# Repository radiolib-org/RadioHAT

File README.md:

# RadioHAT
Raspberry Pi PCIe HAT for radio modules

This HAT is an all-in-one radio modules development platform with the following features. 

* **Built-in logic analyzer** - All pins routed to the transceivers (SPI and various GPIO signals) are also routed to additional Raspberry Pi GPIO pins, to allow the RPi to monitor and record the state of communication pins. See the [pinalyzer repository](https://github.com/radiolib-org/pinalyzer) for details.
* **Adjustable linear voltage regulator** - To supply power-intensive transceivers, there is a dedicated LDO regulator with adjustable output. The output voltage is adjustable between 2.9 and 3.6 V.
* **Power consumption measurement** - There is a built-in INA219 current monitor which allows to measure the power consumption of the transceiver. See the [dc-powermon repository](https://github.com/radiolib-org/dc-powermon) for details.

While these features are useful, they are entirely optional. Without them, the HAT is a simple adapter board for mini-PCIe cards (half-size or full-size) and can be left with most of the components unpopulated, except for the RPi pin header, PCIe connector and the card latch.

## RadioHAT

## Card for modules from Dorji

## Card for modules from GNice-RF

## Card for modules from Ebyte

## Card for Wio-E5

## Mini PCIe connector pinout
Different vendors (RAK Wireless, Waveshare, SeeedStudio and others) offer radio modules in the mini-PCIe card form factor. However, there seems to be no consensus on any specific pinout. Naturally, RadioLib defines its own version to add to the confusion. However, we try to adhere to the standard Mini PCIe 2.0 pinout in the following ways:

* Mini PCIe 2.0 SMB pins are used for I2C
* Mini PCIe 2.0 USB pins are used for USB
* IRQs, resets and various GPIOs are connected to Mini PCIe 2.0 digital signals
* 3.3V voltage pins are used for most modules, though sometimes 5V is optionally used 

The complete pinout of the connector (and therefore the PCIe cards) is shown below.

| Pin | Signal   | Signal   | Pin |
| --- | -------- | -------- | --- |
|   1 | GPIO0    | 3V3      | 2   |
|   3 | IRQ0     | GND      | 4   |
|   5 | IRQ1     | 5V       | 6   |
|   7 | GPIO1    | NC       | 8   |
|   9 | GND      | NC       | 10  |
|  11 | RST0     | NC       | 12  |
|  13 | RST1     | NC       | 14  |
|  15 | GND      | NC       | 16  |
|  17 | NC       | GND      | 18  |
|  19 | NC       | NSS1     | 20  |
|  21 | GND      | NC       | 22  |
|  23 | NC       | 3V3      | 24  |
|  25 | NC       | GND      | 26  |
|  27 | GND      | 5V       | 28  |
|  29 | GND      | I2C_SCL  | 30  |
|  31 | PPS      | I2C_SDA  | 32  |
|  33 | NC       | GND      | 34  |
|  35 | GND      | USB_D-   | 36  |
|  37 | GND      | USB_D+   | 38  |
|  39 | 3V3      | GND      | 40  |
|  41 | 3V3      | LED0     | 42  |
|  43 | GND      | LED1     | 44  |
|  45 | SPI_SCK  | LED2     | 46  |
|  47 | SPI_MISO | 5V       | 48  |
|  49 | SPI_MOSI | GND      | 50  |
|  51 | NSS0     | 3V3      | 52  |

## Raspberry Pi pinout

The shield routes the Mini PCIe connector signals to the following Raspberry Pi GPIO header pins. The pins with prefix `SNS_` are connected to the digital signals through a series resistor and GPIO, allowing to use the RPi as a makeshift logic analyzer.

| Pin | Signal    | Signal    | Pin |
| --- | --------- | --------- | --- |
|   1 | 3V3       | 5V        | 2   |
|   3 | I2C_SCL   | 5V        | 4   |
|   5 | I2C_SDA   | GND       | 6   |
|   7 | SNS_NSS0  | SNS_SDA   | 8   |
|   9 | GND       | SNS_SCL   | 10  |
|  11 | SNS_SCK   | RST0      | 12  |
|  13 | SNS_MISO  | GND       | 14  |
|  15 | SNS_MOSI  | GPIO1     | 16  |
|  17 | 3V3       | IRQ1      | 18  |
|  19 | SPI_MOSI  | GND       | 20  |
|  21 | SPI_MISO  | RST1      | 22  |
|  23 | SPI_SCK   | NSS0      | 24  |
|  25 | GND       | NSS1      | 26  |
|  27 | NC        | NC        | 28  |
|  29 | SNS_IRQ0  | GND       | 30  |
|  31 | SNS_RST0  | SNS_GPIO0 | 32  |
|  33 | SNS_NSS1  | GND       | 34  |
|  35 | SNS_IRQ1  | IRQ0      | 36  |
|  37 | SNS_GPIO1 | GPIO0     | 38  |
|  39 | GND       | SNS_RST1  | 40  |

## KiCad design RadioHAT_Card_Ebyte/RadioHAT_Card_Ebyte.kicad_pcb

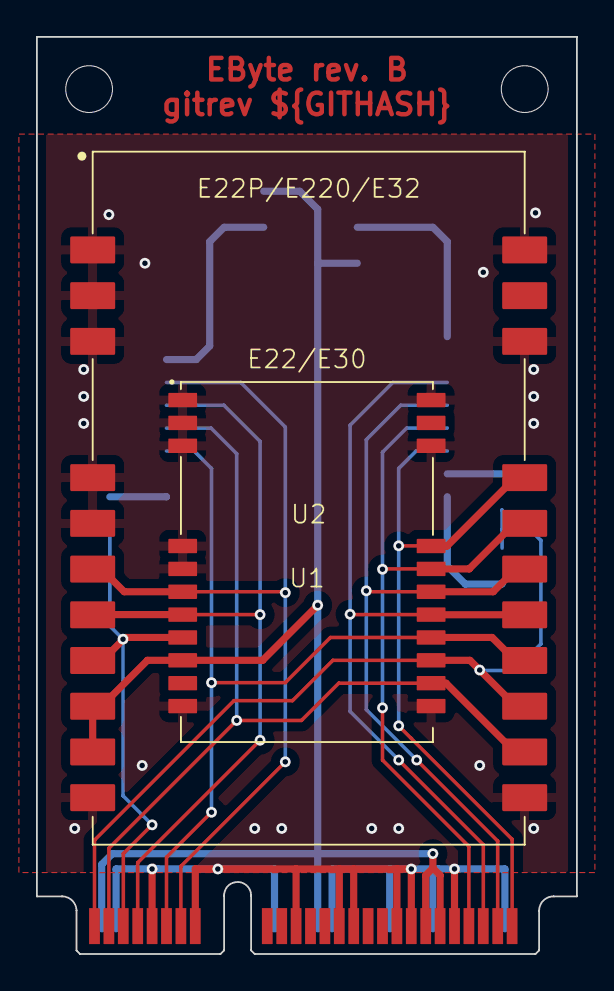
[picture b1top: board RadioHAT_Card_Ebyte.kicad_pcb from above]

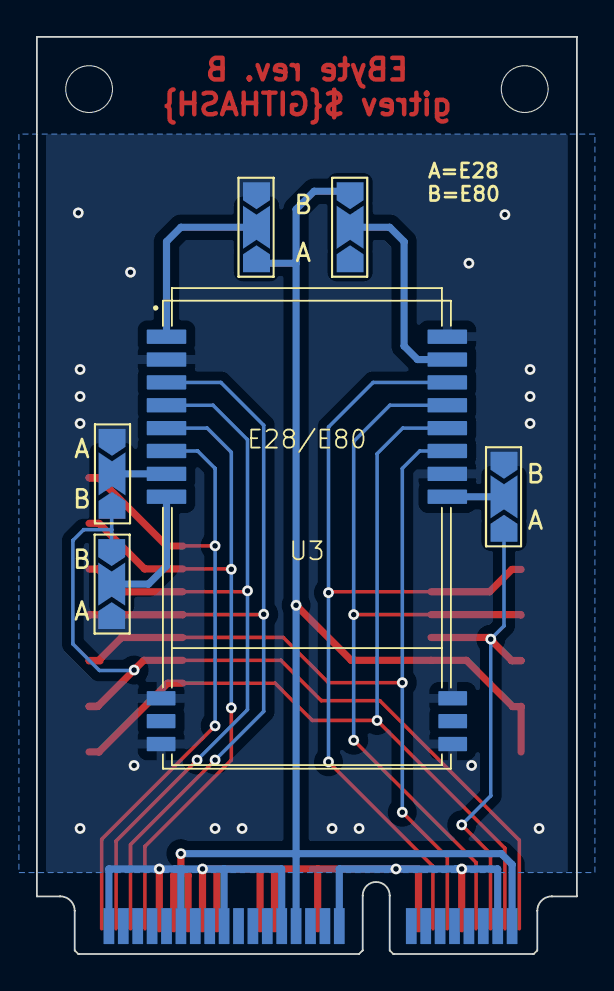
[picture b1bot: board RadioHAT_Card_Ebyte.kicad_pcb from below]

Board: 2 copper layers, 30.0 x 50.9 mm, 9 parts (6 on the bottom side), 17 nets.

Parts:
J1: Mini_PCIe_Full
JP1, JP2, JP3, JP4, JP5: SolderJumper_3_Open; SolderJumper-3_P2.0mm_Open_TrianglePad1.0x1.5mm_NumberLabels
U1: E22_Small
U2: E22_Large
U3: E28_E80

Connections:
+3V3: J1.2 (3V3), J1.24 (3V3), J1.39 (3V3), J1.41 (3V3), JP1.3 (B), JP2.1 (A), U1.9 (VCC), U2.9 (VCC), U2.10 (VCC)
GND: J1.4 (GND), J1.9 (GND), J1.15 (GND), J1.18 (GND), J1.21 (GND), J1.26 (GND), J1.27 (GND), J1.29 (GND), J1.34 (GND), J1.35 (GND), J1.37 (GND), J1.40 (GND), J1.43 (GND), J1.50 (GND), JP2.3 (B), JP3.3 (B), JP4.3 (B), JP5.1 (A), U1.1 (GND), U1.2 (GND), U1.3 (GND), U1.4 (GND), U1.5 (GND), U1.11 (GND), U1.12 (GND), U1.20 (GND_ANT), U1.22 (GND_ANT), U2.1 (GND), U2.2 (GND), U2.3 (GND), U2.4 (GND), U2.5 (GND), U2.11 (GND), U2.12 (GND), U2.20 (GND_ANT), U2.22 (GND_ANT), U3.2 (GND), U3.11 (GND_ANT), U3.13 (GND_ANT), U3.14 (GND_ANT), U3.16 (GND_ANT), U3.20 (GND), U3.26 (GND)
GPIO0: J1.1 (GPIO0), JP3.1 (A), JP5.3 (B), U1.14 (BUSY), U2.14 (BUSY)
GPIO1: J1.7 (GPIO1), U1.7 (TXEN), U2.7 (TXEN), U3.23 (DIO8/DIO1)
IRQ0: J1.3 (IRQ0), U1.13 (DIO1), U2.13 (DIO1), U3.22 (DIO9/BUSY)
IRQ1: J1.5 (IRQ1), JP4.1 (A), U1.8 (DIO2), U2.8 (DIO2)
MISO: J1.47 (SPI_MISO), U1.16 (MISO), U2.16 (MISO), U3.3 (MISO)
MOSI: J1.49 (SPI_MOSI), U1.17 (MOSI), U2.17 (MOSI), U3.4 (MOSI)
NSS: J1.51 (NSS0), U1.19 (NSS), U2.19 (NSS), U3.6 (NSS)
unnamed: JP1.2 (C), U3.25 (VCC/DIO3)
unnamed: JP2.2 (C), U3.1 (GND/VCC)
unnamed: JP3.2 (C), U3.8 (GND/RX_EN)
unnamed: JP4.2 (C), U3.19 (GND/TX_EN)
unnamed: JP5.2 (C), U3.7 (BUSY/GND)
RST0: J1.11 (RST0), U1.15 (NRST), U2.15 (NRST), U3.21 (NRST)
RST1: J1.13 (RST1), U1.6 (RXEN), U2.6 (RXEN), U3.24 (DIO7/DIO2)
SCK: J1.45 (SPI_SCK), U1.18 (SCK), U2.18 (SCK), U3.5 (SCK)

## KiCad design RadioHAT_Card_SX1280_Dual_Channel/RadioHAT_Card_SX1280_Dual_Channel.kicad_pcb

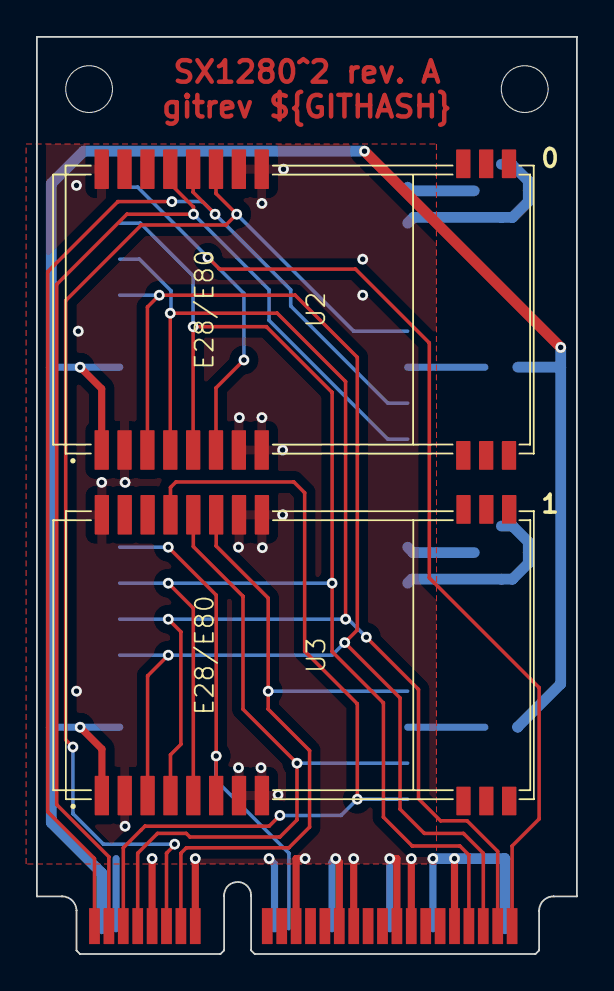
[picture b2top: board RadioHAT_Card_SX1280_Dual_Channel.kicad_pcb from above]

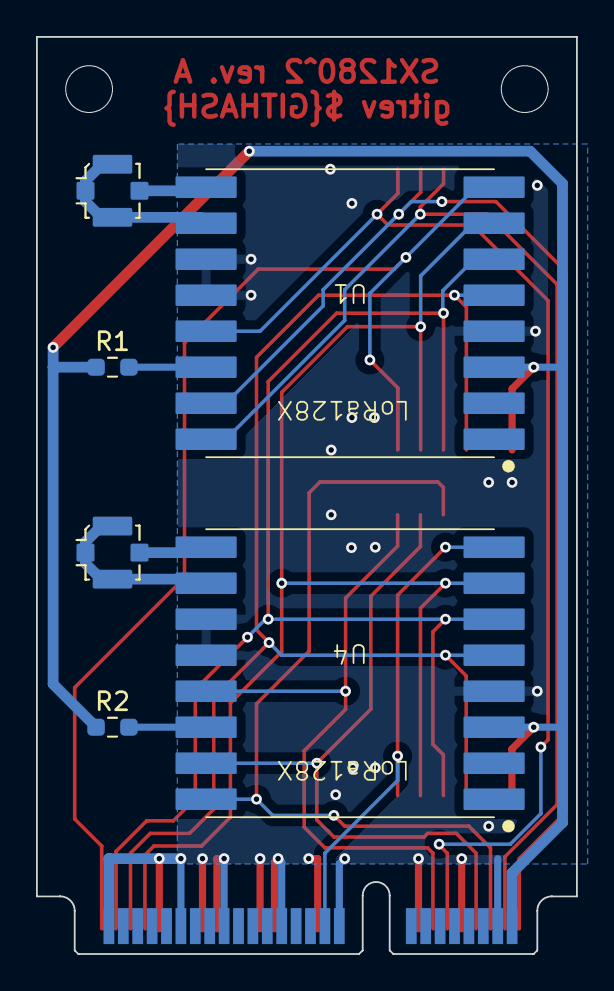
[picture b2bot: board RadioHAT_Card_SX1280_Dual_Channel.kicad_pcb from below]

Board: 2 copper layers, 30.0 x 51.0 mm, 9 parts (6 on the bottom side), 19 nets.

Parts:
J1: Mini_PCIe_Full
J2, J3: Conn_Coaxial; U.FL_Molex_MCRF_73412-0110_Vertical
R1, R2: 1k; R_0603_1608Metric_Pad0.98x0.95mm_HandSolder
U1, U4: LoRa128X
U2, U3: E28_E80

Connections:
+3V3: J1.2 (3V3), R1.1, R2.1, U1.3 (VCC), U2.1 (GND/VCC), U3.1 (GND/VCC), U4.3 (VCC)
GND: J1.4 (GND), J1.9 (GND), J1.15 (GND), J1.18 (GND), J1.21 (GND), J1.26 (GND), J1.27 (GND), J1.29 (GND), J1.34 (GND), J1.35 (GND), J1.37 (GND), J1.40 (GND), J1.43 (GND), J1.50 (GND), U1.4 (GND), U1.11 (GND), U1.12 (GND), U2.2 (GND), U2.7 (BUSY/GND), U2.8 (GND/RX_EN), U2.19 (GND/TX_EN), U2.20 (GND), U2.26 (GND), U3.2 (GND), U3.7 (BUSY/GND), U3.8 (GND/RX_EN), U3.19 (GND/TX_EN), U3.20 (GND), U3.26 (GND), U4.4 (GND), U4.11 (GND), U4.12 (GND)
GPIO0: J1.1 (GPIO0), U1.15 (BUSY), U2.22 (DIO9/BUSY)
GPIO1: J1.7 (GPIO1), U3.22 (DIO9/BUSY), U4.15 (BUSY)
IRQ0: J1.3 (IRQ0), U1.16 (DIO1), U2.23 (DIO8/DIO1)
IRQ1: J1.5 (IRQ1), U3.23 (DIO8/DIO1), U4.16 (DIO1)
MISO: J1.47 (SPI_MISO), U1.5 (MISO), U2.3 (MISO), U3.3 (MISO), U4.5 (MISO)
MOSI: J1.49 (SPI_MOSI), U1.6 (MOSI), U2.4 (MOSI), U3.4 (MOSI), U4.6 (MOSI)
NSS0: J1.51 (NSS0), U1.8 (NSS), U2.6 (NSS)
NSS1: J1.20 (NSS1), U3.6 (NSS), U4.8 (NSS)
unnamed: J2.2 (Ext), U1.10 (GND_ANT)
unnamed: J2.1 (In), U1.9 (ANT)
unnamed: J3.2 (Ext), U4.10 (GND_ANT)
unnamed: J3.1 (In), U4.9 (ANT)
unnamed: R1.2, U1.14 (TCXOEN)
unnamed: R2.2, U4.14 (TCXOEN)
RST0: J1.11 (RST0), U1.13 (NRESET), U2.21 (NRST)
RST1: J1.13 (RST1), U3.21 (NRST), U4.13 (NRESET)
SCK: J1.45 (SPI_SCK), U1.7 (SCK), U2.5 (SCK), U3.5 (SCK), U4.7 (SCK)

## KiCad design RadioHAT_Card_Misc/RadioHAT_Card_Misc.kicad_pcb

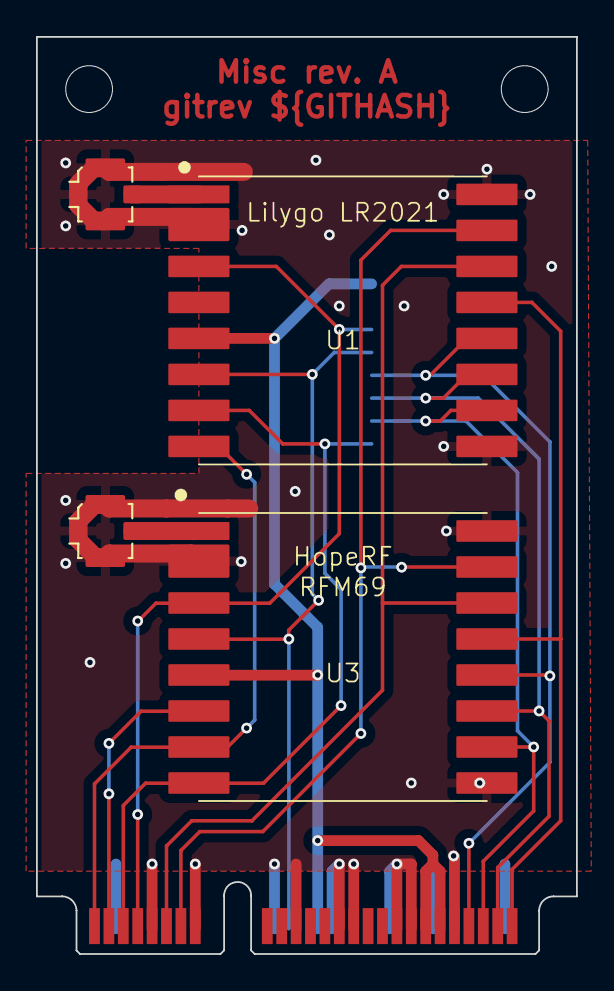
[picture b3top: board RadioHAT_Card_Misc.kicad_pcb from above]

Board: 2 copper layers, 30.0 x 51.0 mm, 6 parts (1 on the bottom side), 15 nets.

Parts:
J1: Mini_PCIe_Full
J2, J3: Conn_Coaxial; U.FL_Molex_MCRF_73412-0110_Vertical
U1: Lilygo_LR2021
U2: nRF24
U3: RFM69

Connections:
+3V3: J1.24 (3V3), J1.39 (3V3), J1.41 (3V3), U1.5 (VCC), U2.1 (+3V3), U3.5 (VCC)
GND: J1.4 (GND), J1.9 (GND), J1.15 (GND), J1.18 (GND), J1.21 (GND), J1.26 (GND), J1.27 (GND), J1.29 (GND), J1.34 (GND), J1.35 (GND), J1.37 (GND), J1.40 (GND), J1.43 (GND), J1.50 (GND), J2.2 (Ext), J3.2 (Ext), U1.2 (GND_ANT), U1.9 (GND), U1.16 (GND), U2.2 (GND), U3.2 (GND), U3.9 (GND), U3.16 (GND)
GPIO0: J1.1 (GPIO0), U1.8 (BUSY), U3.7 (DIO1)
GPIO1: J1.7 (GPIO1), U1.3 (DIO8), U2.3 (CE), U3.3 (DIO3)
IRQ0: J1.3 (IRQ0), U3.6 (DIO0)
IRQ1: J1.5 (IRQ1), U1.7 (DIO11), U2.8 (IRQ), U3.8 (DIO2)
MISO: J1.47 (SPI_MISO), U1.10 (MISO), U2.7 (MISO), U3.10 (MISO)
MOSI: J1.49 (SPI_MOSI), U1.11 (MOSI), U2.6 (MOSI), U3.11 (MOSI)
NSS0: J1.51 (NSS0), U1.13 (NSS), U3.13 (NSS)
NSS1: J1.20 (NSS1), U1.6 (DIO10), U2.4 (CSN), U3.4 (DIO4)
unnamed: J2.1 (In), U1.1 (ANT)
unnamed: J3.1 (In), U3.1 (ANT)
RST0: J1.11 (RST0), U1.14 (NRESET), U3.14 (RST)
RST1: J1.13 (RST1), U1.15 (DIO9), U3.15 (DIO5)
SCK: J1.45 (SPI_SCK), U1.12 (SCK), U2.5 (SCK), U3.12 (SCK)

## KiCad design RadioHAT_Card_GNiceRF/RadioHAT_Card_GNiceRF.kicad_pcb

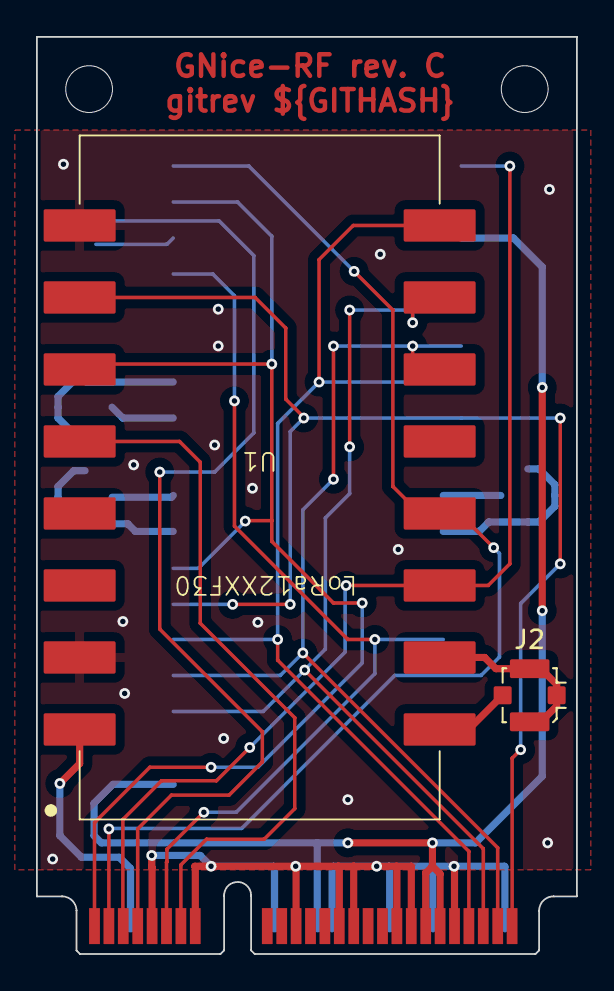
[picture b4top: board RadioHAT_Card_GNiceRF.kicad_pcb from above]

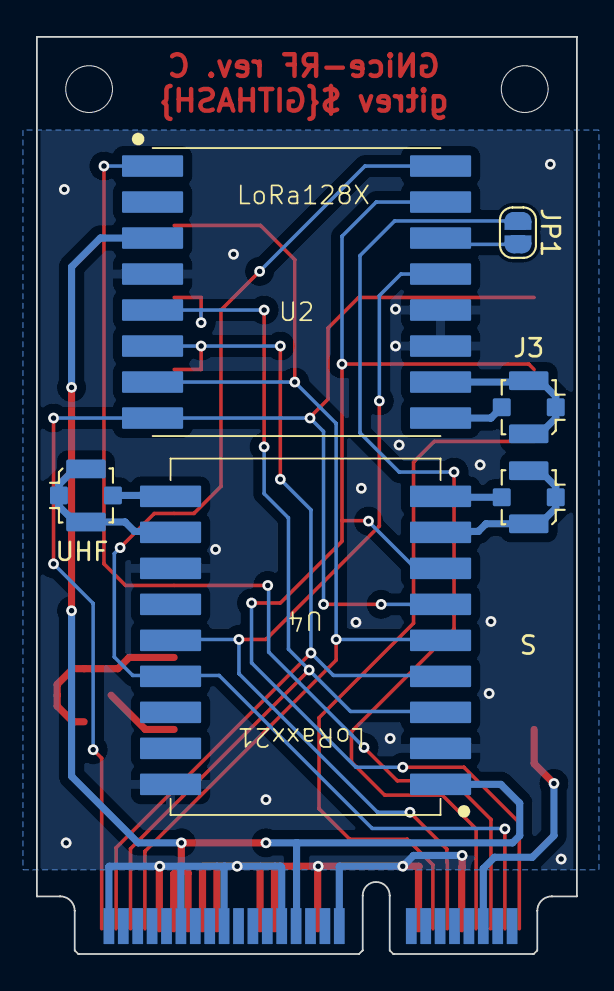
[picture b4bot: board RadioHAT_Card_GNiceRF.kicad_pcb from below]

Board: 2 copper layers, 30.0 x 51.0 mm, 9 parts (6 on the bottom side), 22 nets.

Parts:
J1: Mini_PCIe_Full
J2, J3, J4, J5: Conn_Coaxial; U.FL_Molex_MCRF_73412-0110_Vertical
JP1: SolderJumper_2_Open; SolderJumper-2_P1.3mm_Open_RoundedPad1.0x1.5mm
U1: LoRa12XXF30
U2: LoRa128X
U4: LoRaxx21

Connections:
+3V3: J1.24 (3V3), J1.39 (3V3), J1.41 (3V3), U2.3 (VCC), U4.1 (VCC)
+5V: J1.6 (5V), U1.1 (VCC)
GND: J1.9 (GND), J1.15 (GND), J1.18 (GND), J1.21 (GND), J1.26 (GND), J1.27 (GND), J1.29 (GND), J1.34 (GND), J1.35 (GND), J1.37 (GND), J1.40 (GND), J1.43 (GND), J1.50 (GND), U1.2 (GND), U1.8 (GND), U2.4 (GND), U2.11 (GND), U2.12 (GND), U4.2 (GND), U4.12 (GND), U4.18 (GND)
GPIO0: J1.1 (GPIO0), U1.6 (DIO0(BUSY)), U2.15 (BUSY), U4.7 (BUSY)
GPIO1: J1.7 (GPIO1), JP1.1 (A)
IRQ0: J1.3 (IRQ0), U1.13 (DIO1), U2.16 (DIO1), U4.15 (DIO9)
IRQ1: J1.5 (IRQ1), U1.14 (DIO4(DIO2)), U2.1 (DIO2)
MISO: J1.47 (SPI_MISO), U1.10 (MISO), U2.5 (MISO), U4.3 (MISO)
MOSI: J1.49 (SPI_MOSI), U1.11 (MOSI), U2.6 (MOSI), U4.4 (MOSI)
NSS: J1.51 (NSS0), U1.7 (NSS), U2.8 (NSS), U4.6 (NSS)
unnamed: J2.2 (Ext), U1.15 (GND_ANT)
unnamed: J2.1 (In), U1.16 (ANT)
unnamed: J3.2 (Ext), U2.10 (GND_ANT)
unnamed: J3.1 (In), U2.9 (ANT)
unnamed: J4.2 (Ext), U4.11 (GND_ANT)
unnamed: J4.1 (In), U4.10 (ANT)
unnamed: J5.2 (Ext), U4.8 (GND_ANT)
unnamed: J5.1 (In), U4.9 (2.4/S_ANT)
unnamed: JP1.2 (B), U2.14 (TCXOEN)
RST0: J1.11 (RST0), U2.13 (NRESET), U4.14 (RST)
RST1: J1.13 (RST1), U1.5 (NRESET)
SCK: J1.45 (SPI_SCK), U1.9 (SCK), U2.7 (SCK), U4.5 (SCK)

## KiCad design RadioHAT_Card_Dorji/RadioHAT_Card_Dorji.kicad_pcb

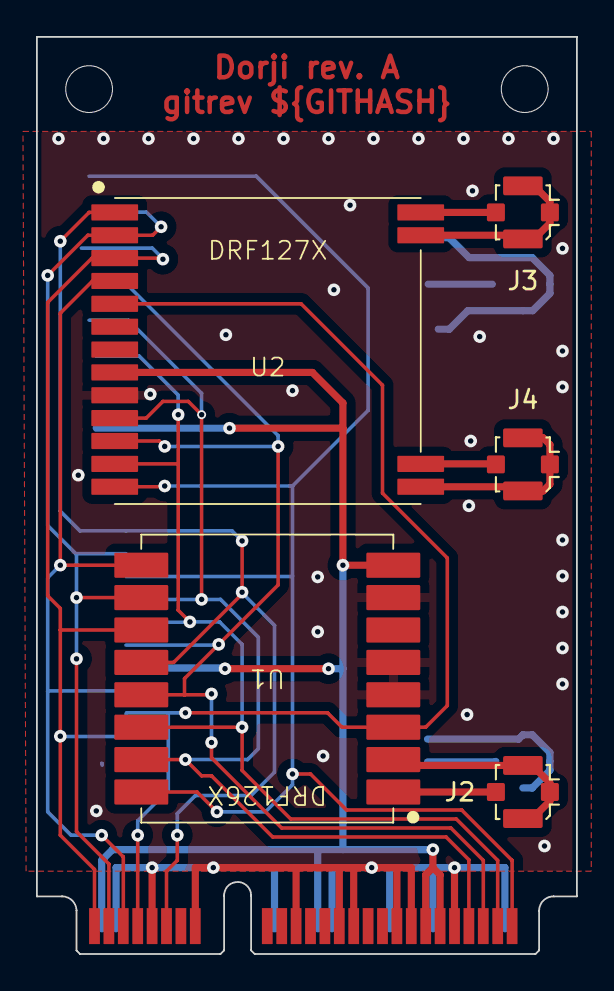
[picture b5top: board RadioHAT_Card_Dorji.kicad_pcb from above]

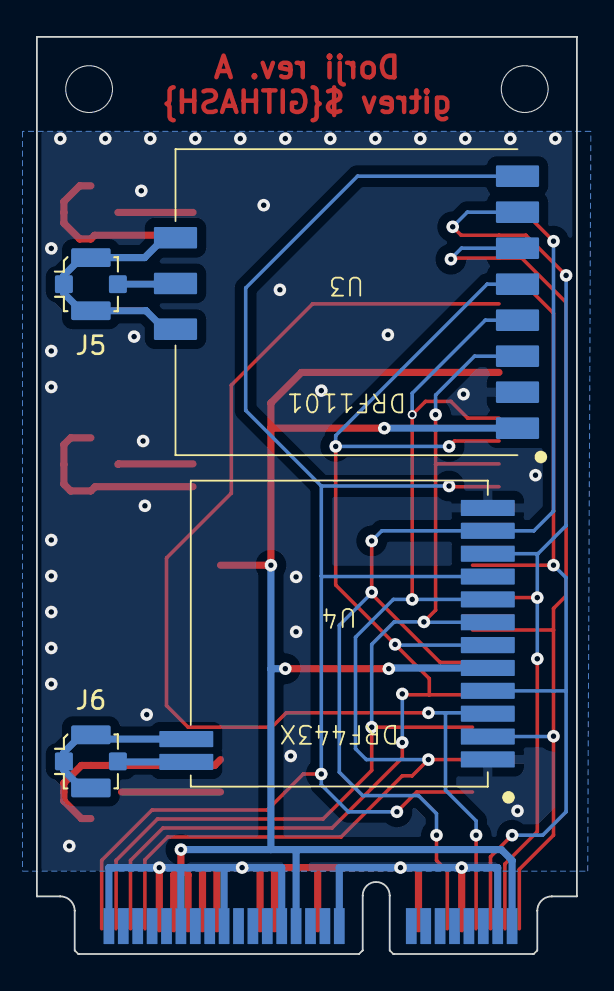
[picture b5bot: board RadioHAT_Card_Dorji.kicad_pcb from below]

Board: 2 copper layers, 30.0 x 51.0 mm, 10 parts (4 on the bottom side), 21 nets.

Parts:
J1: Mini_PCIe_Full
J2, J3, J4, J5, J6: Conn_Coaxial; U.FL_Molex_MCRF_73412-0110_Vertical
U1: DRF126X
U2: DRF127X
U3: DRF1101
U4: DRF443X

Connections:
+3V3: J1.2 (3V3), J1.24 (3V3), J1.39 (3V3), J1.41 (3V3), U1.8 (VDD), U2.8 (VCC), U3.1 (PWR), U4.5 (VCC)
GND: J1.4 (GND), J1.9 (GND), J1.15 (GND), J1.18 (GND), J1.21 (GND), J1.26 (GND), J1.27 (GND), J1.29 (GND), J1.34 (GND), J1.35 (GND), J1.37 (GND), J1.40 (GND), J1.43 (GND), J1.50 (GND), U1.4 (GND), U1.5 (GND), U1.7 (GND), U2.9 (GND), U3.2 (GND), U4.1 (GND), U4.12 (GND)
GPIO0: J1.1 (GPIO0), U1.11 (BUSY), U2.3 (DIO1), U3.6 (GPIO2), U4.2 (GPIO0)
GPIO1: J1.7 (GPIO1), U1.3 (SW), U2.5 (DIO3), U4.3 (GPIO1)
IRQ0: J1.3 (IRQ0), U1.10 (DIO1), U2.2 (DIO0), U3.7 (GPIO0), U4.10 (nIRQ)
IRQ1: J1.5 (IRQ1), U1.9 (DIO2), U2.4 (DIO2), U4.4 (GPIO2)
MISO: J1.47 (SPI_MISO), U1.13 (MISO), U2.11 (MISO), U3.5 (SDO), U4.6 (SDO)
MOSI: J1.49 (SPI_MOSI), U1.14 (MOSI), U2.12 (MOSI), U3.3 (SDI), U4.7 (SDI)
NSS: J1.51 (NSS0), U1.16 (NSS), U2.13 (NSS), U3.8 (CSN), U4.9 (nSEL)
unnamed: J2.2 (Ext), U1.2 (GND_ANT)
unnamed: J2.1 (In), U1.1 (ANT)
unnamed: J3.2 (Ext), U2.16 (GND_SX1278)
unnamed: J3.1 (In), U2.17 (ANT_SX1278)
unnamed: J4.2 (Ext), U2.14 (GND_SX1272)
unnamed: J4.1 (In), U2.15 (ANT_SX1272)
unnamed: J5.2 (Ext), U3.9 (GND_ANT), U3.11 (GND_ANT)
unnamed: J5.1 (In), U3.10 (ANT)
unnamed: J6.2 (Ext), U4.14 (GND_ANT)
unnamed: J6.1 (In), U4.13 (ANT)
RST0: J1.11 (RST0), U1.12 (RST), U2.1 (RESET), U4.11 (SDN)
SCK: J1.45 (SPI_SCK), U1.15 (SCK), U2.10 (SCK), U3.4 (SCLK), U4.8 (SCLK)

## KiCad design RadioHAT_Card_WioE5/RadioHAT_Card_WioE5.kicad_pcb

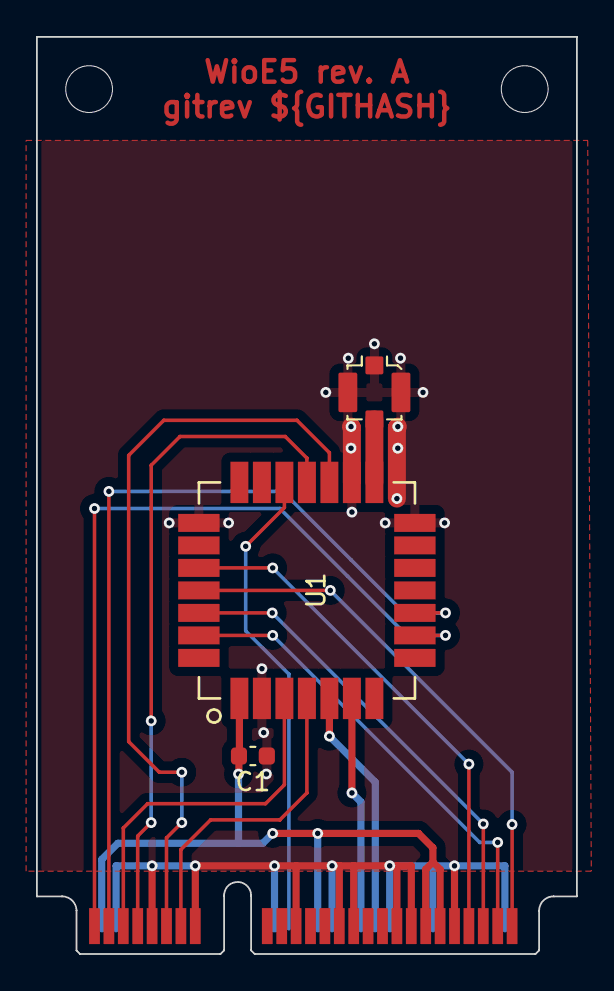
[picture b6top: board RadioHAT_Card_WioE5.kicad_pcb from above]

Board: 2 copper layers, 30.0 x 51.0 mm, 4 parts (0 on the bottom side), 16 nets.

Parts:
C1: 100n; C_0603_1608Metric
J1: Mini_PCIe_Full
J2: Conn_Coaxial; U.FL_Molex_MCRF_73412-0110_Vertical
U1: LoRa-E5

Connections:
+3V3: C1.2, J1.2 (3V3), J1.24 (3V3), J1.39 (3V3), J1.41 (3V3), U1.1 (VCC)
GND: C1.1, J1.4 (GND), J1.9 (GND), J1.15 (GND), J1.18 (GND), J1.21 (GND), J1.26 (GND), J1.27 (GND), J1.29 (GND), J1.34 (GND), J1.35 (GND), J1.37 (GND), J1.40 (GND), J1.43 (GND), J1.50 (GND), J2.2 (Ext), U1.2 (GND), U1.14 (GND), U1.16 (GND), U1.22 (GND)
GPIO0: J1.1 (GPIO0), U1.9 (PB7)
GPIO1: J1.7 (GPIO1), U1.18 (PA3)
IRQ0: J1.3 (IRQ0), U1.10 (PB6)
IRQ1: J1.5 (IRQ1), U1.3 (PA13)
MISO: J1.47 (SPI_MISO), U1.26 (PB14)
MOSI: J1.49 (SPI_MOSI), U1.27 (PA10)
NSS0: J1.51 (NSS0), U1.25 (PB9)
NSS1: J1.20 (NSS1), U1.19 (PA2)
unnamed: J2.1 (In), U1.15 (RFIO)
RST0: J1.11 (RST0), U1.17 (RST)
RST1: J1.13 (RST1), U1.4 (PA14)
SCK: J1.45 (SPI_SCK), U1.24 (PB13~)
SCL: J1.32 (I2C_SCL), U1.5 (PB15)
SDA: J1.30 (I2C_SDA), U1.6 (PA15)

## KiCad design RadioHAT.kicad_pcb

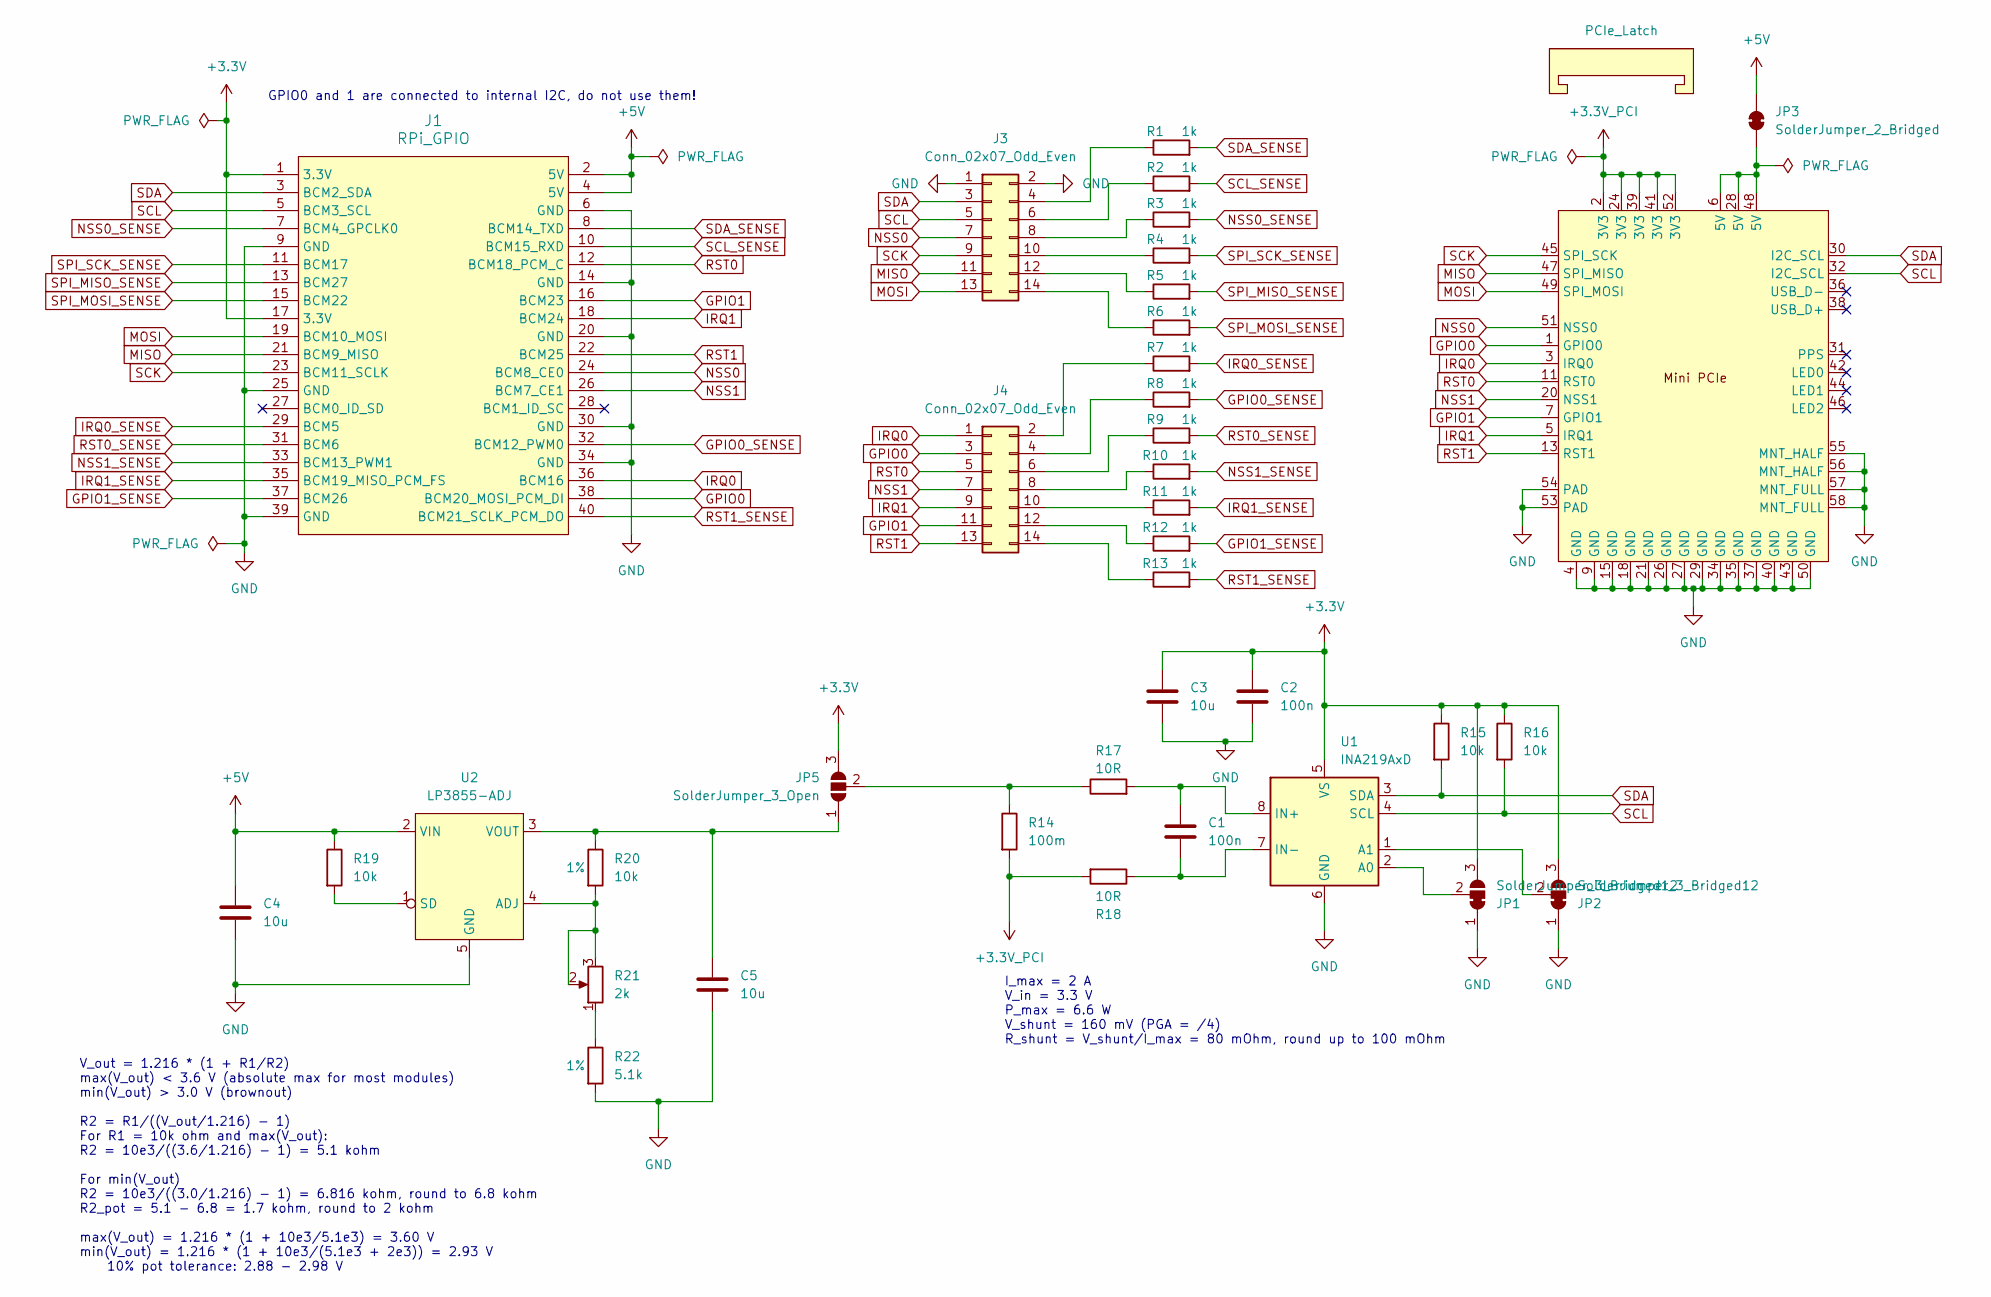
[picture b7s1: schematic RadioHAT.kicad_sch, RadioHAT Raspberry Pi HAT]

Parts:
C1, C2: 100n; C_0603_1608Metric_Pad1.08x0.95mm_HandSolder; Mouser 963-MAJCU168BB7104KT
C3, C4, C5: 10u; C_0805_2012Metric_Pad1.18x1.45mm_HandSolder; Mouser 581-KAM21AR71A106MU
J1: RPi_GPIO; RPI_Hat_B+; Mouser 200-SSQ12004TD
J2: Mini_PCIe_Latch_Hole; Mouser 571-1775838-2
J3, J4: Conn_02x07_Odd_Even; PinHeader_2x07_P2.54mm_Vertical; Mouser 523-G800LW589018EU
JP1, JP2: SolderJumper_3_Bridged12; SolderJumper-3_P1.3mm_Bridged12_Pad1.0x1.5mm_NumberLabels
JP3: SolderJumper_2_Bridged; SolderJumper-2_P1.3mm_Bridged_Pad1.0x1.5mm
JP5: SolderJumper_3_Open; SolderJumper-3_P1.3mm_Open_Pad1.0x1.5mm_NumberLabels
R1, R2, R3, R4, R5, R6, R7, R8, R9, R10, R11, R12, R13: 1k; R_0603_1608Metric_Pad0.98x0.95mm_HandSolder; Mouser 603-AC0603JR-131KL
R14: 100m; R_2512_6332Metric_Pad1.40x3.35mm_HandSolder_Bypass; Mouser 588-PCS2512DR1000ET
R15, R16, R19: 10k; R_0603_1608Metric_Pad0.98x0.95mm_HandSolder; Mouser 603-AF0603FR-0710KL
R17, R18: 10R; R_0603_1608Metric_Pad0.98x0.95mm_HandSolder; Mouser 71-CRCW060310R0FKEAC
R20: 10k; R_0603_1608Metric_Pad0.98x0.95mm_HandSolder; Tolerance 1%; Mouser 603-AF0603FR-0710KL
R21: 2k; Potentiometer_Bourns_3362P1200LF; Mouser 652-3362P-1-202LF
R22: 5.1k; R_0603_1608Metric_Pad0.98x0.95mm_HandSolder; Tolerance 1%; Mouser 279-CRG0603F5K1
U1: INA219AxD; SOIC-8_3.9x4.9mm_P1.27mm; Mouser 595-INA219AIDR
U2: LP3855-ADJ; SOT150P700X180-5N; Mouser 926-LP3855EMPADJNOPB
X1: PCIe_Latch; Mouser 538-48099-5701

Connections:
+3.3V: C2.1, C3.1, J1.1 (3.3V), J1.17 (3.3V), JP1.3 (B), JP2.3 (B), JP5.3 (B), R15.1, R16.1, U1.5 (VS)
+3.3V_PCI: J2.2 (3V3), J2.24 (3V3), J2.39 (3V3), J2.41 (3V3), J2.52 (3V3), R14.2, R18.2
+5V: C4.1, J1.2 (5V), J1.4 (5V), JP3.2 (B), R19.1, U2.2 (VIN)
GND: C2.2, C3.2, C4.2, C5.2, J1.6 (GND), J1.9 (GND), J1.14 (GND), J1.20 (GND), J1.25 (GND), J1.30 (GND), J1.34 (GND), J1.39 (GND), J2.4 (GND), J2.9 (GND), J2.15 (GND), J2.18 (GND), J2.21 (GND), J2.26 (GND), J2.27 (GND), J2.29 (GND), J2.34 (GND), J2.35 (GND), J2.37 (GND), J2.40 (GND), J2.43 (GND), J2.50 (GND), J2.53 (PAD), J2.54 (PAD), J2.55 (MNT_HALF), J2.56 (MNT_HALF), J2.57 (MNT_FULL), J2.58 (MNT_FULL), J3.1, J3.2, JP1.1 (A), JP2.1 (A), R22.2, U1.6 (GND), U2.5 (GND)
GPIO0: J1.38 (BCM20_MOSI_PCM_DI), J2.1 (GPIO0), J4.3
GPIO0_SENSE: J1.32 (BCM12_PWM0), R8.2
GPIO1: J1.16 (BCM23), J2.7 (GPIO1), J4.11
GPIO1_SENSE: J1.37 (BCM26), R12.2
IRQ0: J1.36 (BCM16), J2.3 (IRQ0), J4.1
IRQ0_SENSE: J1.29 (BCM5), R7.2
IRQ1: J1.18 (BCM24), J2.5 (IRQ1), J4.9
IRQ1_SENSE: J1.35 (BCM19_MISO_PCM_FS), R11.2
MISO: J1.21 (BCM9_MISO), J2.47 (SPI_MISO), J3.11
MOSI: J1.19 (BCM10_MOSI), J2.49 (SPI_MOSI), J3.13
NSS0: J1.24 (BCM8_CE0), J2.51 (NSS0), J3.7
NSS0_SENSE: J1.7 (BCM4_GPCLK0), R3.2
NSS1: J1.26 (BCM7_CE1), J2.20 (NSS1), J4.7
NSS1_SENSE: J1.33 (BCM13_PWM1), R10.2
unnamed: J3.4, R1.1
unnamed: J3.6, R2.1
unnamed: J3.8, R3.1
unnamed: J3.10, R4.1
unnamed: J3.12, R5.1
unnamed: J3.14, R6.1
unnamed: J4.2, R7.1
unnamed: J4.4, R8.1
unnamed: J4.6, R9.1
unnamed: J4.8, R10.1
unnamed: J4.10, R11.1
unnamed: J4.12, R12.1
unnamed: J4.14, R13.1
unnamed: JP1.2 (C), U1.2 (A0)
unnamed: JP2.2 (C), U1.1 (A1)
unnamed: J2.6 (5V), J2.28 (5V), J2.48 (5V), JP3.1 (A)
unnamed: C5.1, JP5.1 (A), R20.1, U2.3 (VOUT)
unnamed: JP5.2 (C), R14.1, R17.1
unnamed: R21.1, R22.1
unnamed: C1.1, R17.2, U1.8 (IN+)
unnamed: C1.2, R18.1, U1.7 (IN-)
unnamed: R20.2, R21.2, R21.3, U2.4 (ADJ)
unnamed: R19.2, U2.1 (SD)
RST0: J1.12 (BCM18_PCM_C), J2.11 (RST0), J4.5
RST0_SENSE: J1.31 (BCM6), R9.2
RST1: J1.22 (BCM25), J2.13 (RST1), J4.13
RST1_SENSE: J1.40 (BCM21_SCLK_PCM_DO), R13.2
SCK: J1.23 (BCM11_SCLK), J2.45 (SPI_SCK), J3.9
SCL: J1.5 (BCM3_SCL), J2.32 (I2C_SCL), J3.5, R16.2, U1.4 (SCL)
SCL_SENSE: J1.10 (BCM15_RXD), R2.2
SDA: J1.3 (BCM2_SDA), J2.30 (I2C_SCL), J3.3, R15.2, U1.3 (SDA)
SDA_SENSE: J1.8 (BCM14_TXD), R1.2
SPI_MISO_SENSE: J1.13 (BCM27), R5.2
SPI_MOSI_SENSE: J1.15 (BCM22), R6.2
SPI_SCK_SENSE: J1.11 (BCM17), R4.2

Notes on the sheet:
V_out = 1.216 * (1 + R1/R2) max(V_out) < 3.6 V (absolute max for most modules) min(V_out) > 3.0 V (brownout) R2 = R1/((V_out/1.216) - 1) For R1 = 10k ohm and max(V_out): R2 = 10e3/((3.6/1.216) - 1) = 5.1 kohm For min(V_out) R2 = 10e3/((3.0/1.216) - 1) = 6.816 kohm, round to 6.8 kohm R2_pot = 5.1 - 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
GPIO0 and 1 are connected to internal I2C, do not use them!
I_max = 2 A V_in = 3.3 V P_max = 6.6 W V_shunt = 160 mV (PGA = /4) R_shunt = V_shunt/I_max = 80 mOhm, round up to 100 mOhm

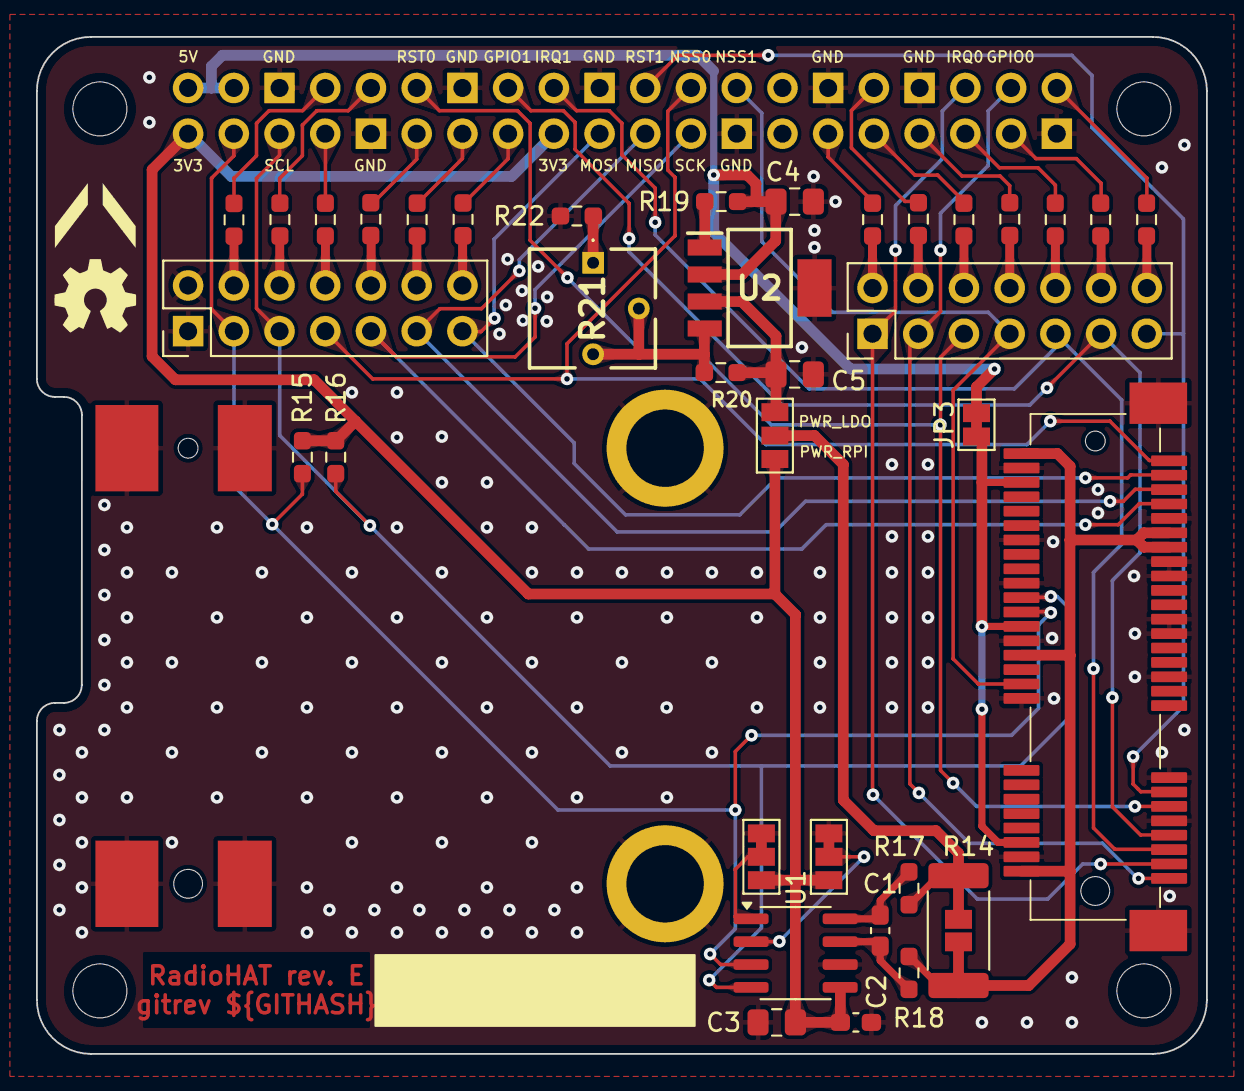
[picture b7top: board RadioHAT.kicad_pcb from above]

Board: 2 copper layers, 65.0 x 56.5 mm, 37 parts (0 on the bottom side), 53 nets.

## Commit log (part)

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2025-07-18 Add HAT template submodule
2025-08-11 Add gitignore for KiCAD projects
2025-08-11 Initial design
2025-08-13 Enables all ERCs as errors and clears up schematic
    - Enabled all ERCs in the schematics as this allows to catch problems early and they are usually sensible
    - Added `no connect` flag on each non connected pin to show that this is intentional
    - Added `Power Flag` symbols on 3V3 and GND close to the pins that actually supply the power to show where the power comes from (and solve the "missing power input" ERC)
    - Moved wires aroudn to prevent visual crossing of unconnected nets to prevent confusion
2025-08-13 Adds courtyard for the minPCI connector and embed its 3d model (1775862-2 from TE)
2025-08-13 Enables all DRCs in PCB editor, fix footprints to comply with DRC, and add 3d models
    - Enabled all DRCs to catch errors early and set default settings of minimum width, spacing and so forth
    - Added courtyard to miniPCI connector to comply with ERC and prevent conflict if more components are placed
    - Increased size of via to 0.7mm diameter, 0.3mm hole to ensure a 0.2mm annular ring (for easier manufacturing)
    - Added 3d model for miniPCI connector (step file is embeded in the footprint)
    - Added 3d model for 2x20 hat connector (using KiCAD default library step file)
2025-08-16 PCIe card slot fix pins, add 3D model and TME link
2025-08-16 [SCH] Treat all ERC issues as errors and fix schematic
2025-08-16 [PCB] Add 3D model to RPI board
2025-08-16 [PCB] Treat all DRC issues as errors and fix layout
2025-08-16 Add PCIe card footprints
2025-08-24 Add Dorji module datasheets
2025-08-24 Add exported 3D file to gitignore
2025-08-24 [PCB] Fix PCIe outline not closed
2025-08-24 [PCB] Remove soldermask from connector pins
2025-08-24 Add Dorji module symbols and footprints
2025-08-24 Add Dorji modules breakout card
2025-08-24 Add pictures to readme
2025-08-25 [PCB] Make card connector edges beveled
2025-08-28 Add 3D models to module footprints
2025-08-28 Change PCIe connector model and add standoff models
2025-08-28 [PCB] Update footprints
2025-08-29 Add pinout to Pi GPIO header
2025-08-29 Add rev0 fab outputs
2025-09-12 [PCB] Fix DRF443x pinout
2025-09-12 [PCB] Adjust radio position to move coax connector away from screw
2025-09-14 Organize docs by manufacturer
2025-09-14 [PCB] Add keepout zones to card screw holes
2025-09-14 [PCB] Minor Dorji card fixes from rev0
2025-09-14 [PCB] Rotate card slot 180 deg, add description, gitrev and logos
2025-09-14 [PCB] Fix DRC warnings
2025-09-15 Add comment explaining DRC exclusion
2025-09-15 Update minimum text size
2025-09-15 [PCB] Add mini PCIe variant with latch
2025-09-15 [PCB] Update HAT layout to use PCIe with latch
2025-09-15 [PCB] Rework modules to isolate antenna ground
2025-09-15 Add GNice-RF modules
2025-09-17 [PCB] Cleanup
2025-09-17 Add manufacturer part numbers
2025-09-17 [PCB] Cleanup, move text
2025-09-17 Add GNiceRF Card
2025-09-17 Fix directory structure
2025-09-18 [PCB] Finalize labels
2025-09-18 [CI] Add KiBot CI
2025-09-18 [CI] Fix KiCAD docker
2025-09-18 [CI] Add KiBot config file
2025-09-18 [PCB] Add git hash tag for CI
2025-09-18 [SCH] Update symbol from library
2025-09-18 [CI] Checkout with submodules
2025-09-19 [CI] Run KiBot for cards
2025-09-19 [CI] Add missing newline
2025-09-19 Fix ERC issues
2025-09-20 Fix library paths
2025-09-20 Update KiBot config
2025-09-20 Change 3D view to top
2025-09-20 Update 3D view
2025-09-20 [PCB] Make githash variable
2025-09-20 [PCB] Make cards' githash variable
2025-09-20 Zoom the 3D view
2025-09-20 Add generated pictures to README
2025-09-20 Remove fab data from repo (only in artifacts)
2025-09-20 Update pictures for rev A
2025-10-04 [PCB] Fix flipped pinout for 12XXF30
2025-10-04 [PCB] Fix minor DRC issue
2025-10-04 [PCB] Update latch footprint to make it easier to solder
2025-10-11 Add Ebyte card
2025-10-12 Add link to Ebyte card render to readme
2025-10-12 Add PCIe pinout table
2025-10-12 [PCB] Cleanup traces
2025-10-12 Add RPi pinout to readme
2025-10-12 [CI] Add Ebyte card to CI
2025-10-12 [SCH] Fix power flags
2025-10-28 Add gridfinity card holder stepfile
2025-10-31 Fix latch keepout zones
2025-10-31 Add packages for rev C HAT
2025-10-31 HAT rev C (GPIO sense, current measure, LDO)
2025-10-31 List rev C features in readme
2025-11-01 Remove RPi HAT submodule
2025-11-01 Move RPi HAT symbol and footprint to project library
2025-11-01 Update to use new RPi HAT
2025-11-01 Fix 4-way connection
2025-11-01 [PCB] Cleanup to move all components to top side
2025-11-01 Rename footprint to match filter
2025-11-01 Add 3D model for RPi connector
2025-11-02 [PCB] Add jumper texts
2025-11-05 [DOC] Add E32 datasheet
2025-11-05 Remove rpi hat library
2025-11-05 Add custom resistor footprint with bypass jumper
2025-11-05 Implemented @RemyChatel recommendations
2025-11-09 [PCB] Use the same package for all 10u caps
2025-11-09 [SCH] Add Mouser part numbers
2025-11-09 Add last remaining Mouser part numbers
2025-11-29 Fix LDO feedback resistors values and part numbers
2025-12-05 Add combined hole/latch PCIe holder
2025-12-05 Update DRC
2025-12-05 [SCH] Move I2C address selection jumpers to 3V3 to simplify layout
2025-12-05 [PCB] Move INA219 to not interfere with large modules
2025-12-07 Add G-Nice RF LRxx21 docs
2025-12-07 Add symbol for GNice-RF LR2021
2025-12-07 Update G-NiceRF card to use LRxx21 instead of LR1120
2025-12-16 Use some PCIe pins as 5V
2025-12-16 Add KiCAD template for cards
2025-12-16 Fix errors in template
2025-12-16 Try to fix library symbol mismatch
2025-12-16 Update for new PCIe symbol
2025-12-16 Fix template card name not centered
2025-12-19 Add courtyard to prevent collisions with bottom-mounted modules
2025-12-19 Fix possible collision with supply voltage solder bridge
2025-12-20 Add 5V power channel for PCI cards
2025-12-20 Fix missing power flag
2025-12-21 Add 5V channel to GNiceRF card
2025-12-21 Add dual-channel SX1280 card
2025-12-22 Minor cleanup
2025-12-22 [CI] Add dual channel card to fab outputs
2025-12-22 [CI] Add dual channel card to DRC and fab steps
2025-12-22 Update symbols to align with library
2025-12-22 Fix pin conflict
2025-12-22 Ignore solder mask bridge errors
2025-12-23 Fix paste on shunt resistor
2025-12-23 Ignore aperture bridges error
2025-12-23 Fix cards stackup
2026-01-10 Add part numbers
2026-01-10 Add LR1120 doc
